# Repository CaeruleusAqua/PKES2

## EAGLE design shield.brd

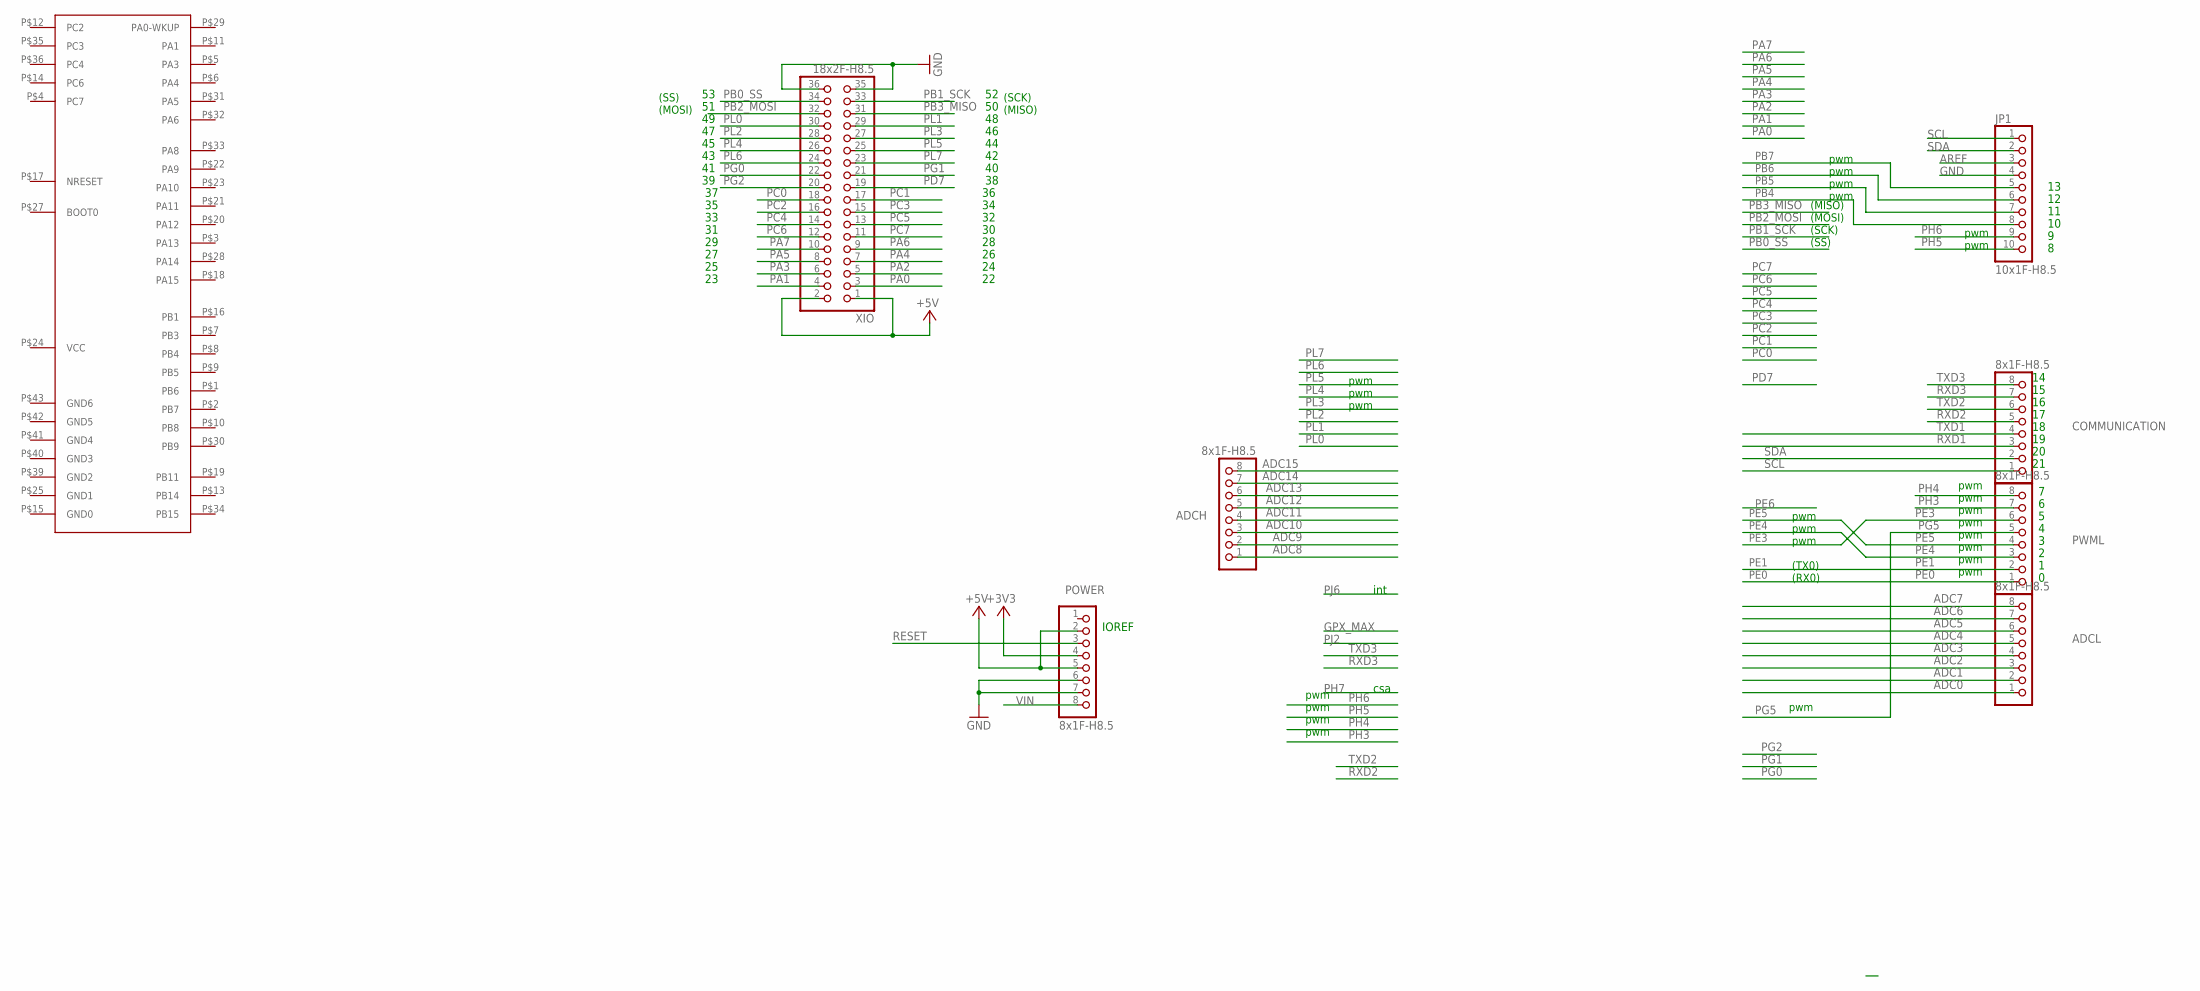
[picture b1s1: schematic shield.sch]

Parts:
ADCH: 8x1F-H8.5; 1X08
ADCL: 8x1F-H8.5; 1X08
COMMUNICATION: 8x1F-H8.5; 1X08
JP1: 10x1F-H8.5; 1X10
POWER: 8x1F-H8.5; 1X08
PWML: 8x1F-H8.5; 1X08
U$1: EMW3162
XIO: 18x2F-H8.5; 2X18

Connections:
+3V3: POWER.4
+5V: POWER.2, POWER.5, XIO.1, XIO.2
ADC0: ADCL.1
ADC1: ADCL.2
ADC2: ADCL.3
ADC3: ADCL.4
ADC4: ADCL.5
ADC5: ADCL.6
ADC6: ADCL.7
ADC7: ADCL.8
ADC8: ADCH.1
ADC9: ADCH.2
ADC10: ADCH.3
ADC11: ADCH.4
ADC12: ADCH.5
ADC13: ADCH.6
ADC14: ADCH.7
ADC15: ADCH.8
AREF: JP1.3
GND: JP1.4, POWER.6, POWER.7, XIO.35, XIO.36
PA0: XIO.3
PA1: XIO.4
PA2: XIO.5
PA3: XIO.6
PA4: XIO.7
PA5: XIO.8
PA6: XIO.9
PA7: XIO.10
PB0_SS: XIO.34
PB1_SCK: XIO.33
PB2_MOSI: XIO.32
PB3_MISO: XIO.31
PB4: JP1.8
PB5: JP1.7
PB6: JP1.6
PB7: JP1.5
PC0: XIO.18
PC1: XIO.17
PC2: XIO.16
PC3: XIO.15
PC4: XIO.14
PC5: XIO.13
PC6: XIO.12
PC7: XIO.11
PD7: XIO.19
PE0: PWML.1
PE1: PWML.2
PE3: PWML.6
PE4: PWML.3
PE5: PWML.4
PG0: XIO.22
PG1: XIO.21
PG2: XIO.20
PG5: PWML.5
PH3: PWML.7
PH4: PWML.8
PH5: JP1.10
PH6: JP1.9
PL0: XIO.30
PL1: XIO.29
PL2: XIO.28
PL3: XIO.27
PL4: XIO.26
PL5: XIO.25
PL6: XIO.24
PL7: XIO.23
RESET: POWER.3
RXD1: COMMUNICATION.3
RXD2: COMMUNICATION.5
RXD3: COMMUNICATION.7
SCL: COMMUNICATION.1, JP1.1
SDA: COMMUNICATION.2, JP1.2
TXD1: COMMUNICATION.4
TXD2: COMMUNICATION.6
TXD3: COMMUNICATION.8
VIN: POWER.8

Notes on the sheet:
pwm
(TX0)
(RX0)
(MISO)
(SCK)
(MOSI)
int
csa
(SS)
IOREF

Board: 2 copper layers, 8 parts (0 on the bottom side), 4 nets, no tracks yet.

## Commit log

2015-06-02 initial git
